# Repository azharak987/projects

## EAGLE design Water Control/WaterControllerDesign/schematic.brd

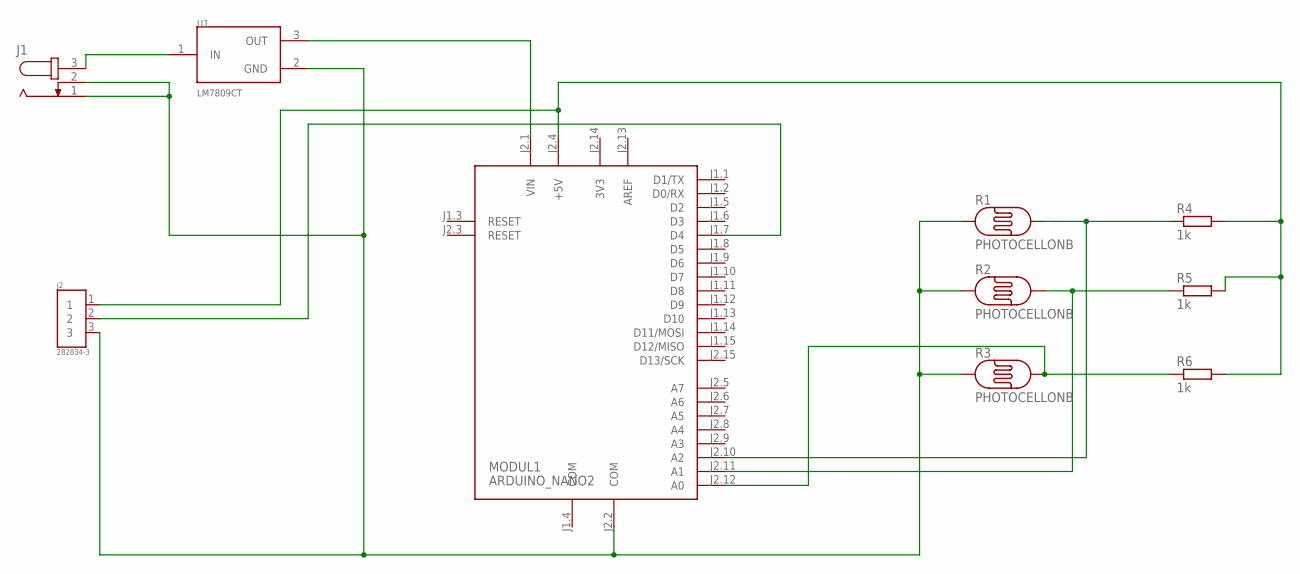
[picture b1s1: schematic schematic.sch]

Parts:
J1: JACK-PLUG1; SPC4078
J2: 282834-3; TE_282834-3
MODUL1: ARDUINO_NANO2
R1, R2, R3: PHOTOCELLONB; ON_BOARD
R4, R5, R6: 1k; 0207/10
U1: LM7809CT; TO254P470X1016X1879-3P

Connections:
3V3: MODUL1.J2.14 (3V3)
AREF: MODUL1.J2.13 (AREF)
COM: MODUL1.J1.4 (COM)
unnamed: MODUL1.J2.10 (A2), R1.2, R4.1
unnamed: MODUL1.J2.11 (A1), R2.2, R5.1
unnamed: MODUL1.J2.12 (A0), R3.2, R6.1
unnamed: J1.1, J1.2, J2.3, MODUL1.J2.2 (COM), R1.1, R2.1, R3.1, U1.2 (GND)
unnamed: J2.1, MODUL1.J2.4 (+5V), R4.2, R5.2, R6.2
unnamed: MODUL1.J2.1 (VIN), U1.3 (OUT)
unnamed: J1.3, U1.1 (IN)
unnamed: J2.2, MODUL1.J1.7 (D4)

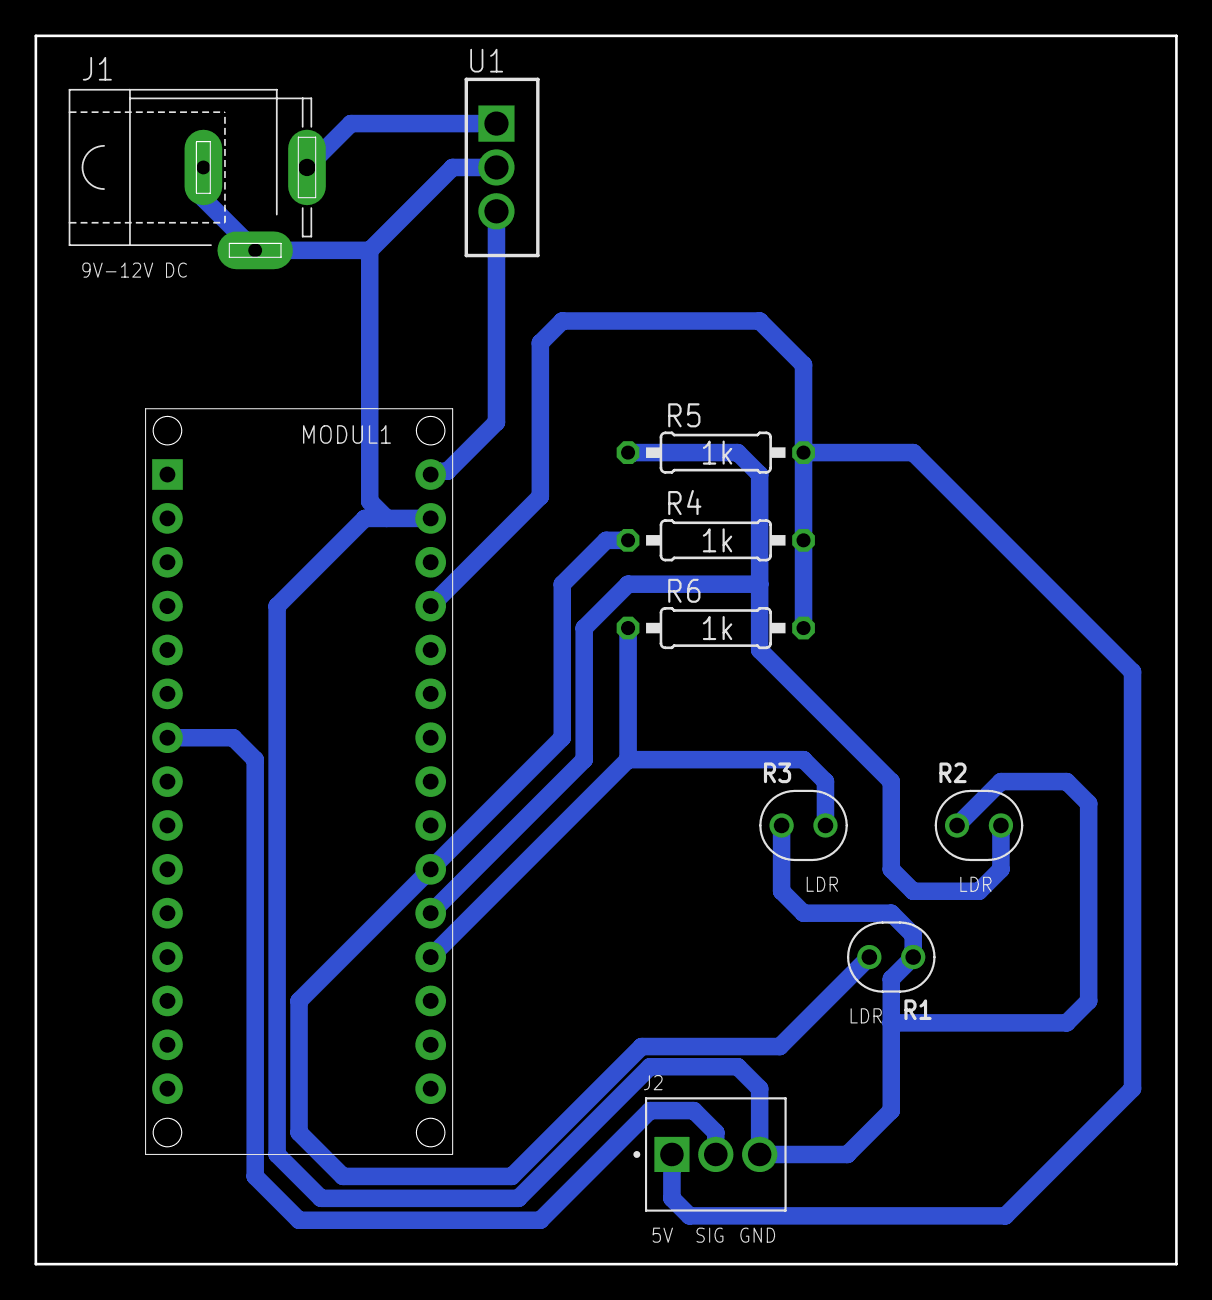
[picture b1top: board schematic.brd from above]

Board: 2 copper layers, 66.0 x 71.1 mm, 10 parts (0 on the bottom side), 8 nets.

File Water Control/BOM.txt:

Partlist exported from C:/Users/azhar/OneDrive/Documents/EAGLE/projects/WaterController/schematic.sch at 21/10/2022 12:18 pm

Part   Value         Device        Package                Description                                                                                          ANZAHL AVAILABILITY COMMENT  DESCRIPTION                                                                    EU_ROHS_COMPLIANCE        MF               MODUL MP       MPN OC_FARNELL OC_NEWARK PACKAGE                   PRICE PURCHASE-URL                                              SPICEMODEL SPICEPREFIX STECKPSI0 STECKPSI1 STECKX0 STECKX1 STECKY0 STECKY1
J1                   JACK-PLUG1    SPC4078                DC POWER JACK                                                                                                                                                                                                                                                                  unknown    unknown                                                                                                                                                                       
J2     282834-3      282834-3      TE_282834-3            Conn; Term Blk; PCB; Wire Receptacle; 3; 2.54mm; 30-16AWG; Green; 10A; 150V; M1.6 Check availability        In Stock     282834-3  3 Position Wire to Board Terminal Block Horizontal with Board 0.100 (2.54mm)  Compliant with Exemptions TE Connectivity        282834-3                          None                      None  https://pricing.snapeda.com/search/part/282834-3/?ref=eda                                                                           
MODUL1 ARDUINO_NANO2 ARDUINO_NANO2 ARDUINO_NANO2          Arduino Nano2                                                                                        2                                                                                                                                                      TRUE                                                                                                                                                                         -76200  76200   177800  177800 
R1     PHOTOCELLONB  PHOTOCELLONB  ON_BOARD               Photo Resitor                                                                                                                                                                                                                                                                                                                                                                                                                                                           
R2     PHOTOCELLONB  PHOTOCELLONB  ON_BOARD               Photo Resitor                                                                                                                                                                                                                                                                                                                                                                                                                                                           
R3     PHOTOCELLONB  PHOTOCELLONB  ON_BOARD               Photo Resitor                                                                                                                                                                                                                                                                                                                                                                                                                                                           
R4     1k            R0207/10      0207/10                RESISTOR, European symbol                                                                                                                                                                                                                                                                                                                                                                     NONE       R                                                              
R5     1k            R0207/10      0207/10                RESISTOR, European symbol                                                                                                                                                                                                                                                                                                                                                                     NONE       R                                                              
R6     1k            R0207/10      0207/10                RESISTOR, European symbol                                                                                                                                                                                                                                                                                                                                                                     NONE       R                                                              
U1     LM7809CT      LM7809CT      TO254P470X1016X1879-3P Standard Regulator Pos 9V 1A 3-Pin(3+Tab) TO-220AB Rail Check availability                                  In Stock               Linear Voltage Regulator IC Positive Fixed 1 Output 1A TO-220-3                                         ON Semiconductor       LM7809CT                          TO-220-3 ON Semiconductor None  https://pricing.snapeda.com/search/part/LM7809CT/?ref=eda

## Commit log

2024-07-22 Added Projects
